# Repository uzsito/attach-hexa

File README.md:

#  

## Description
This project is a configurable low-cost solution to produce fake cooling fan TACH signals for various computer systems. It consists of three main parts:
* Custom pcb with a few cheap components, mounting holes & socket for a replaceable microcontroller
* Arduino Nano or any clone with the same pinout
* Code running on Arduino to handle outputs in a flexible way

With the code uploaded to Arduino, a complete Attach-Hexa is able to drive six computer fan headers (channels) with TACH signals. Users can easily adjust the required RPM simulation on each channel, using pre-defined commands on serial interface.

## Do I need this?
If you have a conventional computer system with ordinary cooling, you don't. However, Attach-Hexa can be useful in the following cases:
* In passively cooled, modded enterprise systems (e.g. home lab), where elimination of "missing fan" alerts is needed to prevent undesired behaviour and ensure proper booting of the system (many servers do not boot at all, if fans are not present)
* In any system with water cooling, where RPM simulation is handy for tuning or testing the setup
* In PWM operation analysis, or other similar hardware development procedure
* In any other case, where generating square-waves is helpful

## Technical Details
TACH signals are used to report the current RPM of cooling fans to the system. Each fan has a dedicated pin for this purpose, usually in the following pinout:

On most motherboard headers, TACH pin is pulled high (+10-12V) by an internal pullup resistor. As the connected fan rotates, it's own built-in electronics (hall-effect sensor, transistor) pulls the TACH line to GND twice in every revolution. This results in a square-wave with a certain period, which is proportional to the fan's rotation speed. So if we would like to reproduce this, we have to pull that pin low at a specified rate. Arduino and similar microcontrollers can do that easily from code. The following schematic represents square-wave generation on channel 1:

The custom pcb board is holding the Arduino Nano, and makes it capable of pulling +12V (or more) lines safely through transistors. The entire unit can be powered from any fan header (using GND & VIN pins) up to +12V, or from USB. The power source is automatically selected to the highest voltage.

## Features
* Six simultaneously working channels
* Built-in LED can be linked to any channel as a visual tracker
* Desired RPMs, LED linked channel and LED frequency settings can be adjusted at runtime
* Serial interface listener to receive commands
* All settings can be saved to EEPROM to survive reboots
* Easily accessible Nano pin headers for potential new features, reserved pins marked on silkscreen

## PCB BOM
The PCB's size is 91mm * 26mm measured by PCBWAY's system. According to KiCAD it is 91,338mm * 25,87mm.

The following components are needed to assemble the custom pcb.

| Component  | Type | Package | Value | Quantity |
| ---------- | ---- | ------- | ----- | -------- |
| R1-R6 | Resistor | SMD-2010 | 4.7kΩ | 6 | 
| Q1-Q6 | Transistor | TO-92 | 2N3904 | 6 | 
| Pin header | Connector | 2.54mm single row | 8-pin male | 1 |
| Pin header | Connector | 2.54mm single row | 15-pin male | 2 |
| Pin socket | Connector | 2.54mm single row | 15-pin female | 2 |

Note: 2N3904 can handle collector current up to 10mA with base resistor 4.7kΩ by forced saturation (current flows from TACH pin to GND through transistor C-E). It is possible to substitute transistors with another type, but keep in mind you have to recalculate base resistor values in this case.

## Serial interface
You can manage Attach-Hexa over serial. Connect USB cable to Arduino, and use any terminal program with the following settings:
* Baud Rate: 115200 | Data: 8bit | Parity: none | Stop bits: 1bit | Flow control: none 
* Local echo: on | Send transmit marker: CR, LF or CR+LF 

Available commands:
* Set any channel RPM: `/channel 2 4000`
* Link LED to channel: `/led link 2`
* Adjust LED delay multiplier to get visible blinking: `/led multi 60`
* Print current settings to terminal: `/print`
* Save current settings to EEPROM: `/save`

| Command element  | Min | Max |
| ---------------- | --- | --- |
| Channel number | 1 | 6 |
| Channel RPM | 1 | 32767 |
| LED link | 1 | 6 |
| LED multiplication | 1 | 255 |

## Assembly and application
1. Clone or download this repository.
2. Use the prebuilt [gerber archive](kicad_board/gerber/attach_hexa.zip) to print the custom pcb. Any chinese manufacturer (JLPCB, ALLPCB, PCBWAY, etc.) can fabricate a copy for a couple dollars. Really, it's dirt cheap.
3. Once you got the pcb and the few listed components, assemble Attach-Hexa by hand soldering, no special tool needed.
4. Upload the [provided code](arduino_sketch/attach_hexa.ino) to an Arduino Nano using Arduino IDE (with [EEPROMex](https://github.com/thijse/Arduino-EEPROMEx) lib installed), and put the Nano in the socket.
5. Connect your terminal application to USB port and use the commands to achieve the desired settings. Save to EEPROM.
6. Place Hexa in the computer you would like to control, and make sure it is powered from that machine's USB port or fan header. Common GND is very important to pull TACH lines properly.
7. Attach channel pins to required TACH pins with dupont wires, and check the simulated RPM in the BIOS/UEFI or OS.

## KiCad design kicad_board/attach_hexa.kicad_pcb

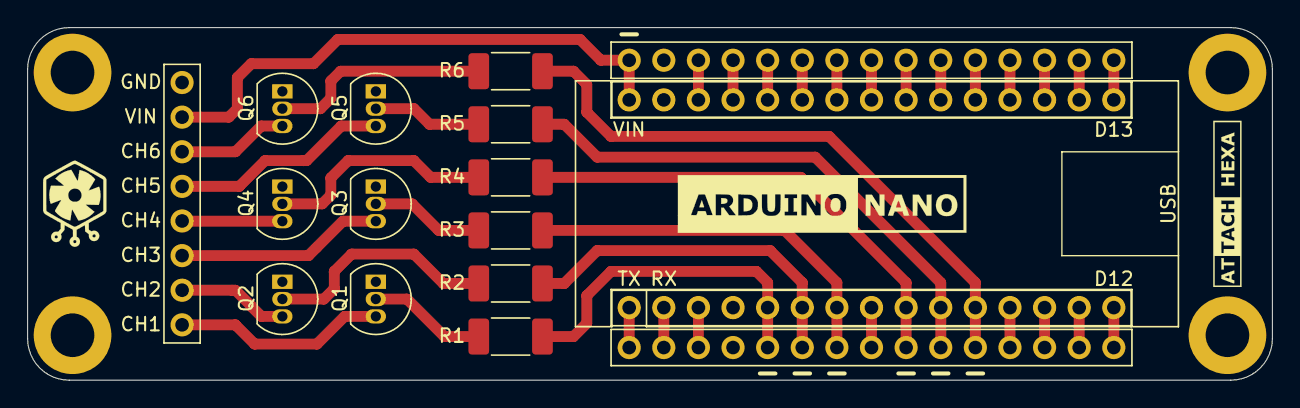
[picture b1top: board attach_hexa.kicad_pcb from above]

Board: 2 copper layers, 91.3 x 25.9 mm, 22 parts (0 on the bottom side), 41 nets.

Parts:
A1: Arduino_Nano_v3.x; Arduino_Nano
H1, H2, H3, H4: MountingHole_Pad; MountingHole_3.2mm_M3_ISO7380_Pad
J1, J5: Conn_01x15_Male; PinHeader_1x15_P2.54mm_Vertical
J2: TACH; PinHeader_1x08_P2.54mm_Vertical
J3, J4: Conn_01x15; PinSocket_1x15_P2.54mm_Vertical
Q1, Q2, Q3, Q4, Q5, Q6: 2N3904; TO-92_Inline
R1, R2, R3, R4, R5, R6: 4,7k; R_2010_5025Metric_Pad1.52x2.65mm_HandSolder

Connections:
GND: A1.4, A1.29, H1.1, H2.1, H3.1, H4.1, J1.14, J2.8, J3.14, J4.4, J5.4, Q1.1, Q2.1, Q3.1, Q4.1, Q5.1, Q6.1
unnamed: A1.1, J4.1, J5.1
unnamed: A1.2, J4.2, J5.2
unnamed: A1.3, J4.3, J5.3
unnamed: A1.5, J4.5, J5.5, R1.2
unnamed: A1.6, J4.6, J5.6, R2.2
unnamed: A1.7, J4.7, J5.7, R3.2
unnamed: A1.8, J4.8, J5.8
unnamed: A1.9, J4.9, J5.9, R4.2
unnamed: A1.10, J4.10, J5.10, R5.2
unnamed: A1.11, J4.11, J5.11, R6.2
unnamed: A1.12, J4.12, J5.12
unnamed: A1.13, J4.13, J5.13
unnamed: A1.14, J4.14, J5.14
unnamed: A1.15, J4.15, J5.15
unnamed: A1.16, J1.1, J3.1
unnamed: A1.17, J1.2, J3.2
unnamed: A1.18, J1.3, J3.3
unnamed: A1.19, J1.4, J3.4
unnamed: A1.20, J1.5, J3.5
unnamed: A1.21, J1.6, J3.6
unnamed: A1.22, J1.7, J3.7
unnamed: A1.23, J1.8, J3.8
unnamed: A1.24, J1.9, J3.9
unnamed: A1.25, J1.10, J3.10
unnamed: A1.26, J1.11, J3.11
unnamed: A1.27, J1.12, J3.12
unnamed: A1.28, J1.13, J3.13
unnamed: A1.30, J1.15, J2.7, J3.15
unnamed: J2.1, Q1.3
unnamed: J2.2, Q2.3
unnamed: J2.3, Q3.3
unnamed: J2.4, Q4.3
unnamed: J2.5, Q5.3
unnamed: J2.6, Q6.3
unnamed: Q1.2, R1.1
unnamed: Q2.2, R2.1
unnamed: Q3.2, R3.1
unnamed: Q4.2, R4.1
unnamed: Q5.2, R5.1
unnamed: Q6.2, R6.1

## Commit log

2020-03-16 Arduino Sketch
2020-03-16 Graphics
2020-03-16 KiCad Project
2020-03-16 Adjusted visibility
2020-03-17 Logic correction
2020-03-18 Header pinout
2020-03-18 Readme ToDo
2020-03-23 Changed SMD sizes to ease hand soldering. Improved silkscreen visibility.
2020-03-24 Updated renders
2020-03-24 Minor trace routing, positioning and silkscreen adjustments
2020-03-24 Set base resistors to 4.7k - force transistor saturation up to 10mA collector current
2020-03-24 Terminal GIF
2020-03-25 Channel schematic
2020-03-25 Adjusted size
2020-03-26 Updated channel graphics
2020-03-30 Added logo
2020-03-30 Updated silkscreen
2020-03-30 Updated render
2020-04-02 Update channel graphics
2020-05-12 Upload gerber files
